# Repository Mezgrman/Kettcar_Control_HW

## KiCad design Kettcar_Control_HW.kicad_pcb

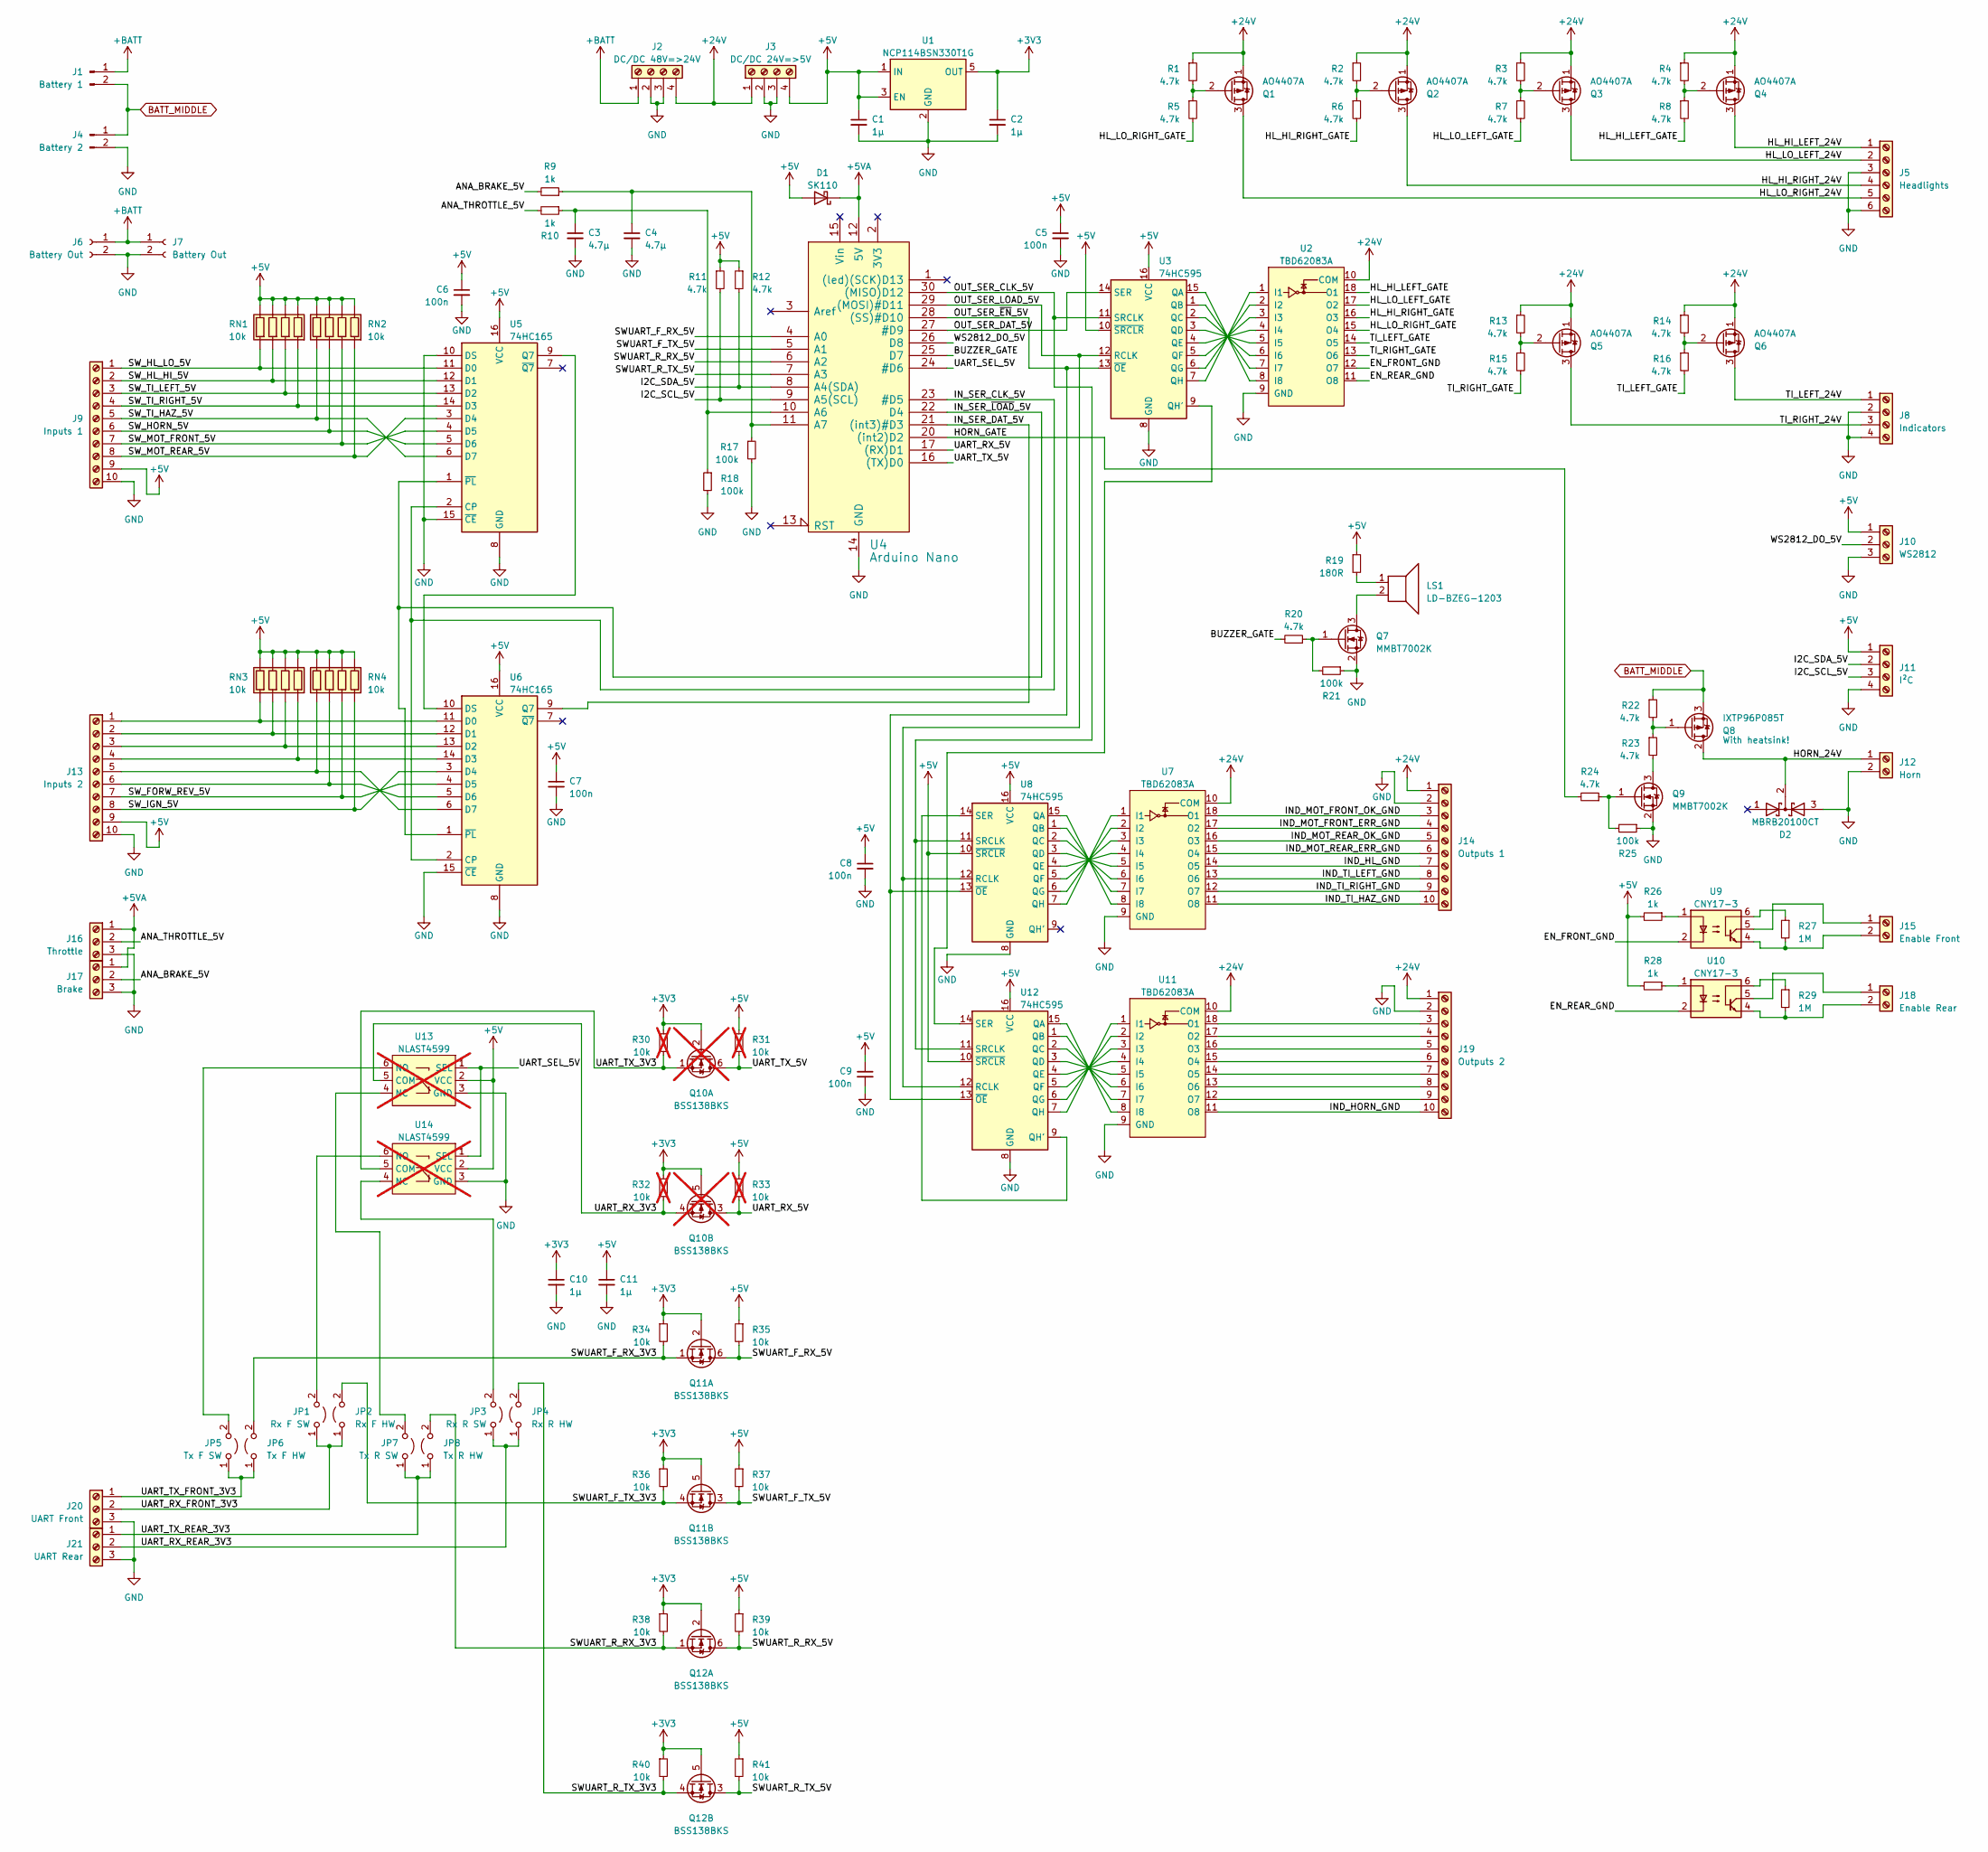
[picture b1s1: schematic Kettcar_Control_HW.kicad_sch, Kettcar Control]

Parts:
C1, C2, C10, C11: 1µ; C_0805_2012Metric
C3, C4: 4.7µ; C_0805_2012Metric
C5, C6, C7, C8, C9: 100n; C_0603_1608Metric
D1: SK110; D_SMB
D2: MBRB20100CT; TO-263-2
J1: Battery 1; Conn_XT90PB
J2: DC/DC 48V=>24V; Conn_DEGSON_2EDGRC-5.0-04P
J3: DC/DC 24V=>5V; Conn_DEGSON_2EDGRC-5.0-04P
J4: Battery 2; Conn_XT90PB
J5: Headlights; Conn_DEGSON_15EDGRC-3.5-06P
J6, J7: Battery Out; Conn_XT60PB
J8: Indicators; Conn_DEGSON_15EDGRC-3.5-04P
J9: Inputs 1; Conn_DEGSON_15EDGRC-3.5-10P
J10: WS2812; Conn_DEGSON_15EDGRC-3.5-03P
J11: I²C; Conn_DEGSON_15EDGRC-3.5-04P
J12: Horn; Conn_DEGSON_2EDGRC-5.0-02P
J13: Inputs 2; Conn_DEGSON_15EDGRC-3.5-10P
J14: Outputs 1; Conn_DEGSON_15EDGRC-3.5-10P
J15: Enable Front; Conn_DEGSON_15EDGRC-3.5-02P
J16: Throttle; Conn_DEGSON_15EDGRC-3.5-03P
J17: Brake; Conn_DEGSON_15EDGRC-3.5-03P
J18: Enable Rear; Conn_DEGSON_15EDGRC-3.5-02P
J19: Outputs 2; Conn_DEGSON_15EDGRC-3.5-10P
J20: UART Front; Conn_DEGSON_15EDGRC-3.5-03P
J21: UART Rear; Conn_DEGSON_15EDGRC-3.5-03P
JP1: Rx F SW; SolderJumper-2_P1.3mm_Open_TrianglePad1.0x1.5mm
JP2: Rx F HW; SolderJumper-2_P1.3mm_Open_TrianglePad1.0x1.5mm
JP3: Rx R SW; SolderJumper-2_P1.3mm_Open_TrianglePad1.0x1.5mm
JP4: Rx R HW; SolderJumper-2_P1.3mm_Open_TrianglePad1.0x1.5mm
JP5: Tx F SW; SolderJumper-2_P1.3mm_Open_TrianglePad1.0x1.5mm
JP6: Tx F HW; SolderJumper-2_P1.3mm_Open_TrianglePad1.0x1.5mm
JP7: Tx R SW; SolderJumper-2_P1.3mm_Open_TrianglePad1.0x1.5mm
JP8: Tx R HW; SolderJumper-2_P1.3mm_Open_TrianglePad1.0x1.5mm
LS1: LD-BZEG-1203; Buzzer_12x9.5RM7.6
Q1, Q2, Q3, Q4, Q5, Q6: AO4407A; SO8_FET
Q7, Q9: MMBT7002K; SOT-23-3
Q8: IXTP96P085T; TO-220-3_Vertical
Q10: BSS138BKS; SOT-363_SC-70-6; not fitted
Q11, Q12: BSS138BKS; SOT-363_SC-70-6
R1, R2, R3, R4, R5, R6, R7, R8, R11, R12, R13, R14, R15, R16, R20, R22, R23, R24: 4.7k; R_0603_1608Metric
R9, R10, R26, R28: 1k; R_0603_1608Metric
R17, R18, R21, R25: 100k; R_0603_1608Metric
R19: 180R; R_0603_1608Metric
R27, R29: 1M; R_0603_1608Metric
R30, R31, R32, R33: 10k; R_0603_1608Metric; not fitted
R34, R35, R36, R37, R38, R39, R40, R41: 10k; R_0603_1608Metric
RN1, RN2, RN3, RN4: 10k; R_Array_Concave_4x0603
U1: NCP114BSN330T1G; TSOT-23-5
U2, U7, U11: TBD62083A; SSOP-18_4.4x6.5mm_P0.65mm
U3, U8, U12: 74HC595; SOIC-16_3.9x9.9mm_P1.27mm
U4: Arduino Nano; Arduino_Nano
U5, U6: 74HC165; SOIC-16_3.9x9.9mm_P1.27mm
U9, U10: CNY17-3; Optocoupler_SMD_6pin
U13, U14: NLAST4599; SOT-363_SC-70-6; not fitted

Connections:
+3V3: C2.1, C10.1, Q10.2 (G), Q10.5 (G), Q11.2 (G), Q11.5 (G), Q12.2 (G), Q12.5 (G), R30.1, R32.1, R34.1, R36.1, R38.1, R40.1, U1.5 (OUT)
+5V: C1.1, C5.1, C6.1, C7.1, C8.1, C9.1, C11.1, D1.2 (A), J3.4, J9.9, J10.1, J11.1, J13.9, R11.1, R12.1, R19.1, R26.2, R28.2, R31.1, R33.1, R35.1, R37.1, R39.1, R41.1, RN1.5, RN1.6, RN1.7, RN1.8, RN2.5, RN2.6, RN2.7, RN2.8, RN3.5, RN3.6, RN3.7, RN3.8, RN4.5, RN4.6, RN4.7, RN4.8, U1.1 (IN), U1.3 (EN), U3.10 (~SRCLR), U3.16 (VCC), U5.16 (VCC), U6.16 (VCC), U8.10 (~SRCLR), U8.16 (VCC), U12.10 (~SRCLR), U12.16 (VCC), U13.2 (VCC), U14.2 (VCC)
+5VA: D1.1 (K), J16.1, J17.1, U4.12 (5V)
+24V: J2.4, J3.1, J14.1, J19.1, Q1.1 (S), Q2.1 (S), Q3.1 (S), Q4.1 (S), Q5.1 (S), Q6.1 (S), R1.1, R2.1, R3.1, R4.1, R13.1, R14.1, U2.10 (COM), U7.10 (COM), U11.10 (COM)
+BATT: J1.1, J2.1, J6.1, J7.1
/ANA_BRAKE_5V: J17.2, R9.2
/ANA_THROTTLE_5V: J16.2, R10.2
/BUZZER_GATE: R20.2, U4.25 (D7)
/EN_FRONT_GND: U2.12 (O7), U9.2
/EN_REAR_GND: U2.11 (O8), U10.2
/HL_HI_LEFT_24V: J5.1, Q4.3 (D)
/HL_HI_LEFT_GATE: R8.2, U2.18 (O1)
/HL_HI_RIGHT_24V: J5.4, Q2.3 (D)
/HL_HI_RIGHT_GATE: R6.2, U2.16 (O3)
/HL_LO_LEFT_24V: J5.2, Q3.3 (D)
/HL_LO_LEFT_GATE: R7.2, U2.17 (O2)
/HL_LO_RIGHT_24V: J5.5, Q1.3 (D)
/HL_LO_RIGHT_GATE: R5.2, U2.15 (O4)
/HORN_24V: D2.2 (K), J12.1, Q8.2 (D)
/HORN_GATE: R24.2, U4.20 ((int2)D2)
/I2C_SCL_5V: J11.3, R11.2, U4.9 (A5(SCL))
/I2C_SDA_5V: J11.2, R12.2, U4.8 (A4(SDA))
/IND_HL_GND: J14.7, U7.14 (O5)
/IND_HORN_GND: J19.10, U11.11 (O8)
/IND_MOT_FRONT_ERR_GND: J14.4, U7.17 (O2)
/IND_MOT_FRONT_OK_GND: J14.3, U7.18 (O1)
/IND_MOT_REAR_ERR_GND: J14.6, U7.15 (O4)
/IND_MOT_REAR_OK_GND: J14.5, U7.16 (O3)
/IND_TI_HAZ_GND: J14.10, U7.11 (O8)
/IND_TI_LEFT_GND: J14.8, U7.13 (O6)
/IND_TI_RIGHT_GND: J14.9, U7.12 (O7)
/IN_SER_CLK_5V: U4.23 (#D5), U5.2 (CP), U6.2 (CP)
/IN_SER_DAT_5V: U4.21 ((int3)#D3), U6.9 (Q7)
/IN_SER_~LOAD_5V: U4.22 (D4), U5.1 (~PL), U6.1 (~PL)
/OUT_SER_CLK_5V: U3.11 (SRCLK), U4.30 ((MISO)D12), U8.11 (SRCLK), U12.11 (SRCLK)
/OUT_SER_DAT_5V: U3.14 (SER), U4.27 (#D9)
/OUT_SER_LOAD_5V: U3.12 (RCLK), U4.29 ((MOSI)#D11), U8.12 (RCLK), U12.12 (RCLK)
/OUT_SER_~EN_5V: U3.13 (~OE), U4.28 ((SS)#D10), U8.13 (~OE), U12.13 (~OE)
/SWUART_F_RX_3V3: JP6.2 (B), Q11.1 (S), R34.2
/SWUART_F_RX_5V: Q11.6 (D), R35.2, U4.4 (A0)
/SWUART_F_TX_3V3: JP2.2 (B), Q11.4 (S), R36.2
/SWUART_F_TX_5V: Q11.3 (D), R37.2, U4.5 (A1)
/SWUART_R_RX_3V3: JP8.2 (B), Q12.1 (S), R38.2
/SWUART_R_RX_5V: Q12.6 (D), R39.2, U4.6 (A2)
/SWUART_R_TX_3V3: JP4.2 (B), Q12.4 (S), R40.2
/SWUART_R_TX_5V: Q12.3 (D), R41.2, U4.7 (A3)
/SW_FORW_REV_5V: J13.7, RN4.2, U6.4 (D5)
/SW_HL_HI_5V: J9.2, RN1.3, U5.12 (D1)
/SW_HL_LO_5V: J9.1, RN1.4, U5.11 (D0)
/SW_HORN_5V: J9.6, RN2.3, U5.5 (D6)
/SW_IGN_5V: J13.8, RN4.1, U6.3 (D4)
/SW_MOT_FRONT_5V: J9.7, RN2.2, U5.4 (D5)
/SW_MOT_REAR_5V: J9.8, RN2.1, U5.3 (D4)
/SW_TI_HAZ_5V: J9.5, RN2.4, U5.6 (D7)
/SW_TI_LEFT_5V: J9.3, RN1.2, U5.13 (D2)
/SW_TI_RIGHT_5V: J9.4, RN1.1, U5.14 (D3)
/TI_LEFT_24V: J8.1, Q6.3 (D)
/TI_LEFT_GATE: R16.2, U2.14 (O5)
/TI_RIGHT_24V: J8.3, Q5.3 (D)
/TI_RIGHT_GATE: R15.2, U2.13 (O6)
/UART_RX_3V3: Q10.4 (S), R32.2, U13.5 (COM)
/UART_RX_5V: Q10.3 (D), R33.2, U4.17 ((RX)D1)
/UART_RX_FRONT_3V3: J20.2, JP1.1 (A), JP2.1 (A)
/UART_RX_REAR_3V3: J21.2, JP3.1 (A), JP4.1 (A)
/UART_SEL_5V: U4.24 (#D6), U13.1 (SEL), U14.1 (SEL)
/UART_TX_3V3: Q10.1 (S), R30.2, U14.5 (COM)
/UART_TX_5V: Q10.6 (D), R31.2, U4.16 ((TX)D0)
/UART_TX_FRONT_3V3: J20.1, JP5.1 (A), JP6.1 (A)
/UART_TX_REAR_3V3: J21.1, JP7.1 (A), JP8.1 (A)
/WS2812_DO_5V: J10.2, U4.26 (D8)
BATT_MIDDLE: J1.2, J4.1, Q8.3 (S), R22.1
GND: C1.2, C2.2, C3.2, C4.2, C5.2, C6.2, C7.2, C8.2, C9.2, C10.2, C11.2, D2.3 (A), J2.2, J2.3, J3.2, J3.3, J4.2, J5.3, J5.6, J6.2, J7.2, J8.2, J8.4, J9.10, J10.3, J11.4, J12.2, J13.10, J14.2, J16.3, J17.3, J19.2, J20.3, J21.3, Q7.2 (S), Q9.2 (S), R17.2, R18.2, R21.1, R25.1, U1.2 (GND), U2.9 (GND), U3.8 (GND), U4.14 (GND), U4.19 (GND), U5.8 (GND), U5.10 (DS), U5.15 (~CE), U6.8 (GND), U6.15 (~CE), U7.9 (GND), U8.8 (GND), U11.9 (GND), U12.8 (GND), U13.3 (GND), U14.3 (GND)
unnamed: J13.1, RN3.4, U6.11 (D0)
unnamed: J13.2, RN3.3, U6.12 (D1)
unnamed: J13.3, RN3.2, U6.13 (D2)
unnamed: J13.4, RN3.1, U6.14 (D3)
unnamed: J13.5, RN4.4, U6.6 (D7)
unnamed: J13.6, RN4.3, U6.5 (D6)
unnamed: J15.1, U9.5
unnamed: J15.2, R27.2, U9.4
unnamed: J18.1, U10.5
unnamed: J18.2, R29.2, U10.4
unnamed: J19.3, U11.18 (O1)
unnamed: J19.4, U11.17 (O2)
unnamed: J19.5, U11.16 (O3)
unnamed: J19.6, U11.15 (O4)
unnamed: J19.7, U11.14 (O5)
unnamed: J19.8, U11.13 (O6)
unnamed: J19.9, U11.12 (O7)
unnamed: JP1.2 (B), U14.6 (NO)
unnamed: JP3.2 (B), U14.4 (NC)
unnamed: JP5.2 (B), U13.6 (NO)
unnamed: JP7.2 (B), U13.4 (NC)
unnamed: LS1.1, R19.2
unnamed: Q1.2 (G), R1.2, R5.1
unnamed: Q2.2 (G), R2.2, R6.1
unnamed: Q3.2 (G), R3.2, R7.1
unnamed: Q4.2 (G), R4.2, R8.1
unnamed: Q5.2 (G), R13.2, R15.1
unnamed: Q6.2 (G), R14.2, R16.1
unnamed: LS1.2, Q7.3 (D)
unnamed: Q7.1 (G), R20.1, R21.2
unnamed: Q8.1 (G), R22.2, R23.1
unnamed: Q9.3 (D), R23.2
unnamed: Q9.1 (G), R24.1, R25.2
unnamed: R26.1, U9.1
unnamed: R27.1, U9.6
unnamed: R28.1, U10.1
unnamed: R29.1, U10.6
unnamed: U2.1 (I1), U3.7 (QH)
unnamed: U2.2 (I2), U3.6 (QG)
unnamed: U2.3 (I3), U3.5 (QF)
unnamed: U2.4 (I4), U3.4 (QE)
unnamed: U2.5 (I5), U3.3 (QD)
unnamed: U2.6 (I6), U3.2 (QC)
unnamed: U2.7 (I7), U3.1 (QB)
unnamed: U2.8 (I8), U3.15 (QA)
unnamed: C3.1, R10.1, R18.1, U4.10 (A6)
unnamed: C4.1, R9.1, R17.1, U4.11 (A7)
unnamed: U5.9 (Q7), U6.10 (DS)
unnamed: U7.1 (I1), U8.7 (QH)
unnamed: U7.2 (I2), U8.6 (QG)
unnamed: U7.3 (I3), U8.5 (QF)
unnamed: U7.4 (I4), U8.4 (QE)
unnamed: U7.5 (I5), U8.3 (QD)
unnamed: U7.6 (I6), U8.2 (QC)
unnamed: U7.7 (I7), U8.1 (QB)
unnamed: U7.8 (I8), U8.15 (QA)
unnamed: U11.1 (I1), U12.7 (QH)
unnamed: U11.2 (I2), U12.6 (QG)
unnamed: U11.3 (I3), U12.5 (QF)
unnamed: U11.4 (I4), U12.4 (QE)
unnamed: U11.5 (I5), U12.3 (QD)
unnamed: U11.6 (I6), U12.2 (QC)
unnamed: U11.7 (I7), U12.1 (QB)
unnamed: U11.8 (I8), U12.15 (QA)
unnamed: U8.14 (SER), U12.9 (QH')
unnamed: U3.9 (QH'), U12.14 (SER)

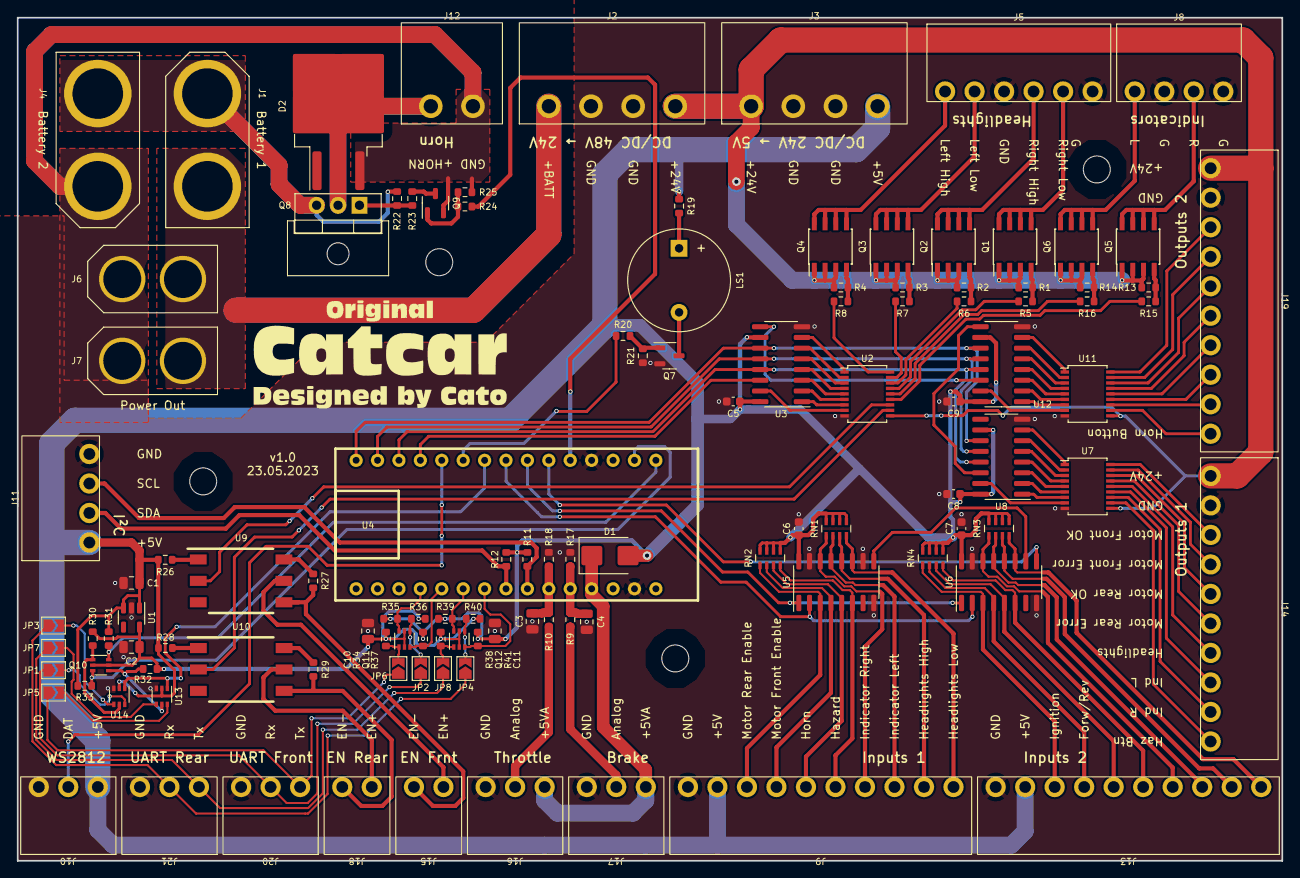
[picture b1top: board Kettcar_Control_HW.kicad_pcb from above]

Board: 2 copper layers, 150.0 x 100.0 mm, 114 parts (0 on the bottom side), 138 nets.

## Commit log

2023-06-05 Remove "do not populate" status for HW UART components
